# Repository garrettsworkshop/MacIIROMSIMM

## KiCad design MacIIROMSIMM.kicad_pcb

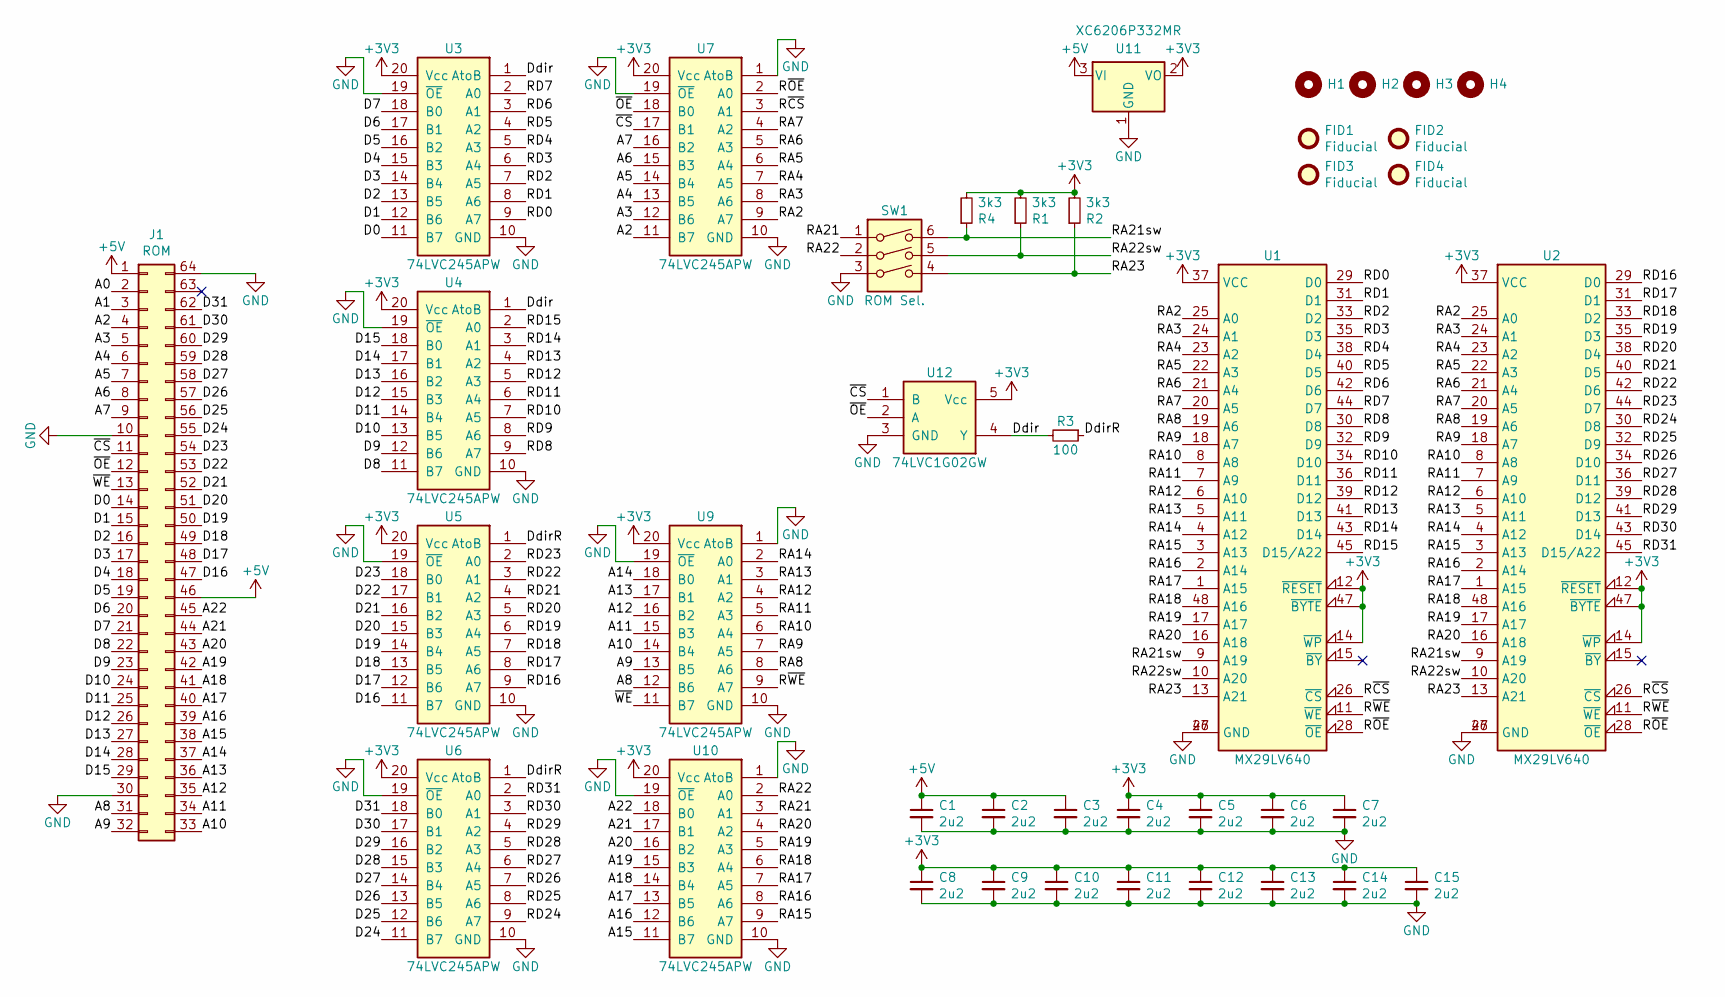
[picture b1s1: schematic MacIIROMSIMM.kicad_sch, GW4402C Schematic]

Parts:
C1, C2, C3, C4, C5, C6, C7, C8, C9, C10, C11, C12, C13, C14, C15: 2u2; C_0603; LCSC Part C23630
FID1, FID2, FID3, FID4: Fiducial
H1, H2, H3, H4: PasteHole_1.152mm_NPTH
J1: ROM; MacIIROMSIMM_Edge
R1, R2, R4: 3k3; R_0603; LCSC Part C22978
R3: 100; R_0603; LCSC Part C22775
SW1: ROM Sel.; SW_DIP_SPSTx03_Slide_DSHP03TS_P1.27mm; LCSC Part C319051
U1, U2: MX29LV640; TSOP-I-48_18.4x12mm_P0.5mm; LCSC Part C30076
U3, U4, U5, U6, U7, U9, U10: 74LVC245APW; TSSOP-20_4.4x6.5mm_P0.65mm; LCSC Part C6082
U11: XC6206P332MR; SOT-23; LCSC Part C5446
U12: 74LVC1G02GW; SOT-353; LCSC Part C353856

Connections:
+3V3: C4.1, C5.1, C6.1, C7.1, C8.1, C9.1, C10.1, C11.1, C12.1, C13.1, C14.1, C15.1, R1.2, R2.2, R4.2, U1.12 (~RESET), U1.14 (~WP), U1.37 (VCC), U1.47 (~BYTE), U2.12 (~RESET), U2.14 (~WP), U2.37 (VCC), U2.47 (~BYTE), U3.20 (Vcc), U4.20 (Vcc), U5.20 (Vcc), U6.20 (Vcc), U7.20 (Vcc), U9.20 (Vcc), U10.20 (Vcc), U11.2 (VO), U12.5 (Vcc)
+5V: C1.1, C2.1, C3.1, J1.1, J1.46, U11.3 (VI)
/A0: J1.2
/A1: J1.3
/A2: J1.4, U7.11 (B7)
/A3: J1.5, U7.12 (B6)
/A4: J1.6, U7.13 (B5)
/A5: J1.7, U7.14 (B4)
/A6: J1.8, U7.15 (B3)
/A7: J1.9, U7.16 (B2)
/A8: J1.31, U9.12 (B6)
/A9: J1.32, U9.13 (B5)
/A10: J1.33, U9.14 (B4)
/A11: J1.34, U9.15 (B3)
/A12: J1.35, U9.16 (B2)
/A13: J1.36, U9.17 (B1)
/A14: J1.37, U9.18 (B0)
/A15: J1.38, U10.11 (B7)
/A16: J1.39, U10.12 (B6)
/A17: J1.40, U10.13 (B5)
/A18: J1.41, U10.14 (B4)
/A19: J1.42, U10.15 (B3)
/A20: J1.43, U10.16 (B2)
/A21: J1.44, U10.17 (B1)
/A22: J1.45, U10.18 (B0)
/D0: J1.14, U3.11 (B7)
/D1: J1.15, U3.12 (B6)
/D2: J1.16, U3.13 (B5)
/D3: J1.17, U3.14 (B4)
/D4: J1.18, U3.15 (B3)
/D5: J1.19, U3.16 (B2)
/D6: J1.20, U3.17 (B1)
/D7: J1.21, U3.18 (B0)
/D8: J1.22, U4.11 (B7)
/D9: J1.23, U4.12 (B6)
/D10: J1.24, U4.13 (B5)
/D11: J1.25, U4.14 (B4)
/D12: J1.26, U4.15 (B3)
/D13: J1.27, U4.16 (B2)
/D14: J1.28, U4.17 (B1)
/D15: J1.29, U4.18 (B0)
/D16: J1.47, U5.11 (B7)
/D17: J1.48, U5.12 (B6)
/D18: J1.49, U5.13 (B5)
/D19: J1.50, U5.14 (B4)
/D20: J1.51, U5.15 (B3)
/D21: J1.52, U5.16 (B2)
/D22: J1.53, U5.17 (B1)
/D23: J1.54, U5.18 (B0)
/D24: J1.55, U6.11 (B7)
/D25: J1.56, U6.12 (B6)
/D26: J1.57, U6.13 (B5)
/D27: J1.58, U6.14 (B4)
/D28: J1.59, U6.15 (B3)
/D29: J1.60, U6.16 (B2)
/D30: J1.61, U6.17 (B1)
/D31: J1.62, U6.18 (B0)
/Ddir: R3.2, U3.1 (AtoB), U4.1 (AtoB), U12.4 (Y)
/DdirR: R3.1, U5.1 (AtoB), U6.1 (AtoB)
/RA2: U1.25 (A0), U2.25 (A0), U7.9 (A7)
/RA3: U1.24 (A1), U2.24 (A1), U7.8 (A6)
/RA4: U1.23 (A2), U2.23 (A2), U7.7 (A5)
/RA5: U1.22 (A3), U2.22 (A3), U7.6 (A4)
/RA6: U1.21 (A4), U2.21 (A4), U7.5 (A3)
/RA7: U1.20 (A5), U2.20 (A5), U7.4 (A2)
/RA8: U1.19 (A6), U2.19 (A6), U9.8 (A6)
/RA9: U1.18 (A7), U2.18 (A7), U9.7 (A5)
/RA10: U1.8 (A8), U2.8 (A8), U9.6 (A4)
/RA11: U1.7 (A9), U2.7 (A9), U9.5 (A3)
/RA12: U1.6 (A10), U2.6 (A10), U9.4 (A2)
/RA13: U1.5 (A11), U2.5 (A11), U9.3 (A1)
/RA14: U1.4 (A12), U2.4 (A12), U9.2 (A0)
/RA15: U1.3 (A13), U2.3 (A13), U10.9 (A7)
/RA16: U1.2 (A14), U2.2 (A14), U10.8 (A6)
/RA17: U1.1 (A15), U2.1 (A15), U10.7 (A5)
/RA18: U1.48 (A16), U2.48 (A16), U10.6 (A4)
/RA19: U1.17 (A17), U2.17 (A17), U10.5 (A3)
/RA20: U1.16 (A18), U2.16 (A18), U10.4 (A2)
/RA21: SW1.1, U10.3 (A1)
/RA21sw: R4.1, SW1.6, U1.9 (A19), U2.9 (A19)
/RA22: SW1.2, U10.2 (A0)
/RA22sw: R1.1, SW1.5, U1.10 (A20), U2.10 (A20)
/RA23: R2.1, SW1.4, U1.13 (A21), U2.13 (A21)
/RD0: U1.29 (D0), U3.9 (A7)
/RD1: U1.31 (D1), U3.8 (A6)
/RD2: U1.33 (D2), U3.7 (A5)
/RD3: U1.35 (D3), U3.6 (A4)
/RD4: U1.38 (D4), U3.5 (A3)
/RD5: U1.40 (D5), U3.4 (A2)
/RD6: U1.42 (D6), U3.3 (A1)
/RD7: U1.44 (D7), U3.2 (A0)
/RD8: U1.30 (D8), U4.9 (A7)
/RD9: U1.32 (D9), U4.8 (A6)
/RD10: U1.34 (D10), U4.7 (A5)
/RD11: U1.36 (D11), U4.6 (A4)
/RD12: U1.39 (D12), U4.5 (A3)
/RD13: U1.41 (D13), U4.4 (A2)
/RD14: U1.43 (D14), U4.3 (A1)
/RD15: U1.45 (D15/A22), U4.2 (A0)
/RD16: U2.29 (D0), U5.9 (A7)
/RD17: U2.31 (D1), U5.8 (A6)
/RD18: U2.33 (D2), U5.7 (A5)
/RD19: U2.35 (D3), U5.6 (A4)
/RD20: U2.38 (D4), U5.5 (A3)
/RD21: U2.40 (D5), U5.4 (A2)
/RD22: U2.42 (D6), U5.3 (A1)
/RD23: U2.44 (D7), U5.2 (A0)
/RD24: U2.30 (D8), U6.9 (A7)
/RD25: U2.32 (D9), U6.8 (A6)
/RD26: U2.34 (D10), U6.7 (A5)
/RD27: U2.36 (D11), U6.6 (A4)
/RD28: U2.39 (D12), U6.5 (A3)
/RD29: U2.41 (D13), U6.4 (A2)
/RD30: U2.43 (D14), U6.3 (A1)
/RD31: U2.45 (D15/A22), U6.2 (A0)
/R~CS: U1.26 (~CS), U2.26 (~CS), U7.3 (A1)
/R~OE: U1.28 (~OE), U2.28 (~OE), U7.2 (A0)
/R~WE: U1.11 (~WE), U2.11 (~WE), U9.9 (A7)
/~CS: J1.11, U7.17 (B1), U12.1 (B)
/~OE: J1.12, U7.18 (B0), U12.2 (A)
/~WE: J1.13, U9.11 (B7)
GND: C1.2, C2.2, C3.2, C4.2, C5.2, C6.2, C7.2, C8.2, C9.2, C10.2, C11.2, C12.2, C13.2, C14.2, C15.2, J1.10, J1.30, J1.64, SW1.3, U1.27 (GND), U1.46 (GND), U2.27 (GND), U2.46 (GND), U3.10 (GND), U3.19 (~OE), U4.10 (GND), U4.19 (~OE), U5.10 (GND), U5.19 (~OE), U6.10 (GND), U6.19 (~OE), U7.1 (AtoB), U7.10 (GND), U7.19 (~OE), U9.1 (AtoB), U9.10 (GND), U9.19 (~OE), U10.1 (AtoB), U10.10 (GND), U10.19 (~OE), U11.1 (GND), U12.3 (GND)

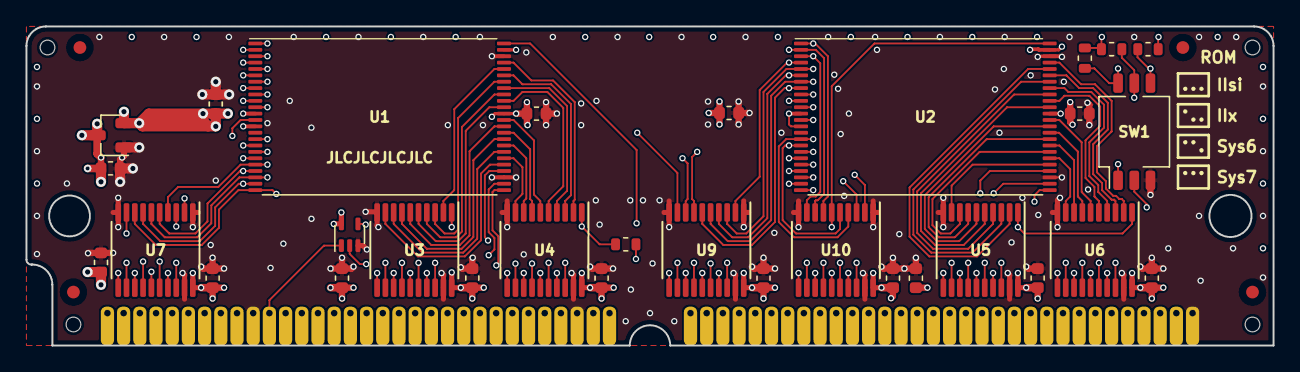
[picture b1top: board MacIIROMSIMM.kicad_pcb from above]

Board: 4 copper layers, 97.8 x 25.0 mm, 40 parts (0 on the bottom side), 120 nets.

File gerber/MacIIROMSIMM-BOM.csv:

"Reference","Quantity","Value","Footprint","LCSC Part","DNP"
"C1, C2, C3, C4, C5, C6, C7, C8, C9, C10, C11, C12, C13, C14, C15","15","2u2","stdpads:C_0603","C23630",""
"FID1, FID2, FID3, FID4","4","Fiducial","stdpads:Fiducial","",""
"H1, H2, H3, H4","4","","stdpads:PasteHole_1.152mm_NPTH","",""
"J1","1","ROM","stdpads:MacIIROMSIMM_Edge","",""
"R1, R2, R4","3","3k3","stdpads:R_0603","C22978",""
"R3","1","100","stdpads:R_0603","C22775",""
"SW1","1","ROM Sel.","stdpads:SW_DIP_SPSTx03_Slide_DSHP03TS_P1.27mm","C319051",""
"U1, U2","2","MX29LV640","stdpads:TSOP-I-48_18.4x12mm_P0.5mm","C30076",""
"U3, U4, U5, U6, U7, U9, U10","7","74LVC245APW","stdpads:TSSOP-20_4.4x6.5mm_P0.65mm","C6082",""
"U11","1","XC6206P332MR","stdpads:SOT-23","C5446",""
"U12","1","74LVC1G02GW","stdpads:SOT-353","C353856",""

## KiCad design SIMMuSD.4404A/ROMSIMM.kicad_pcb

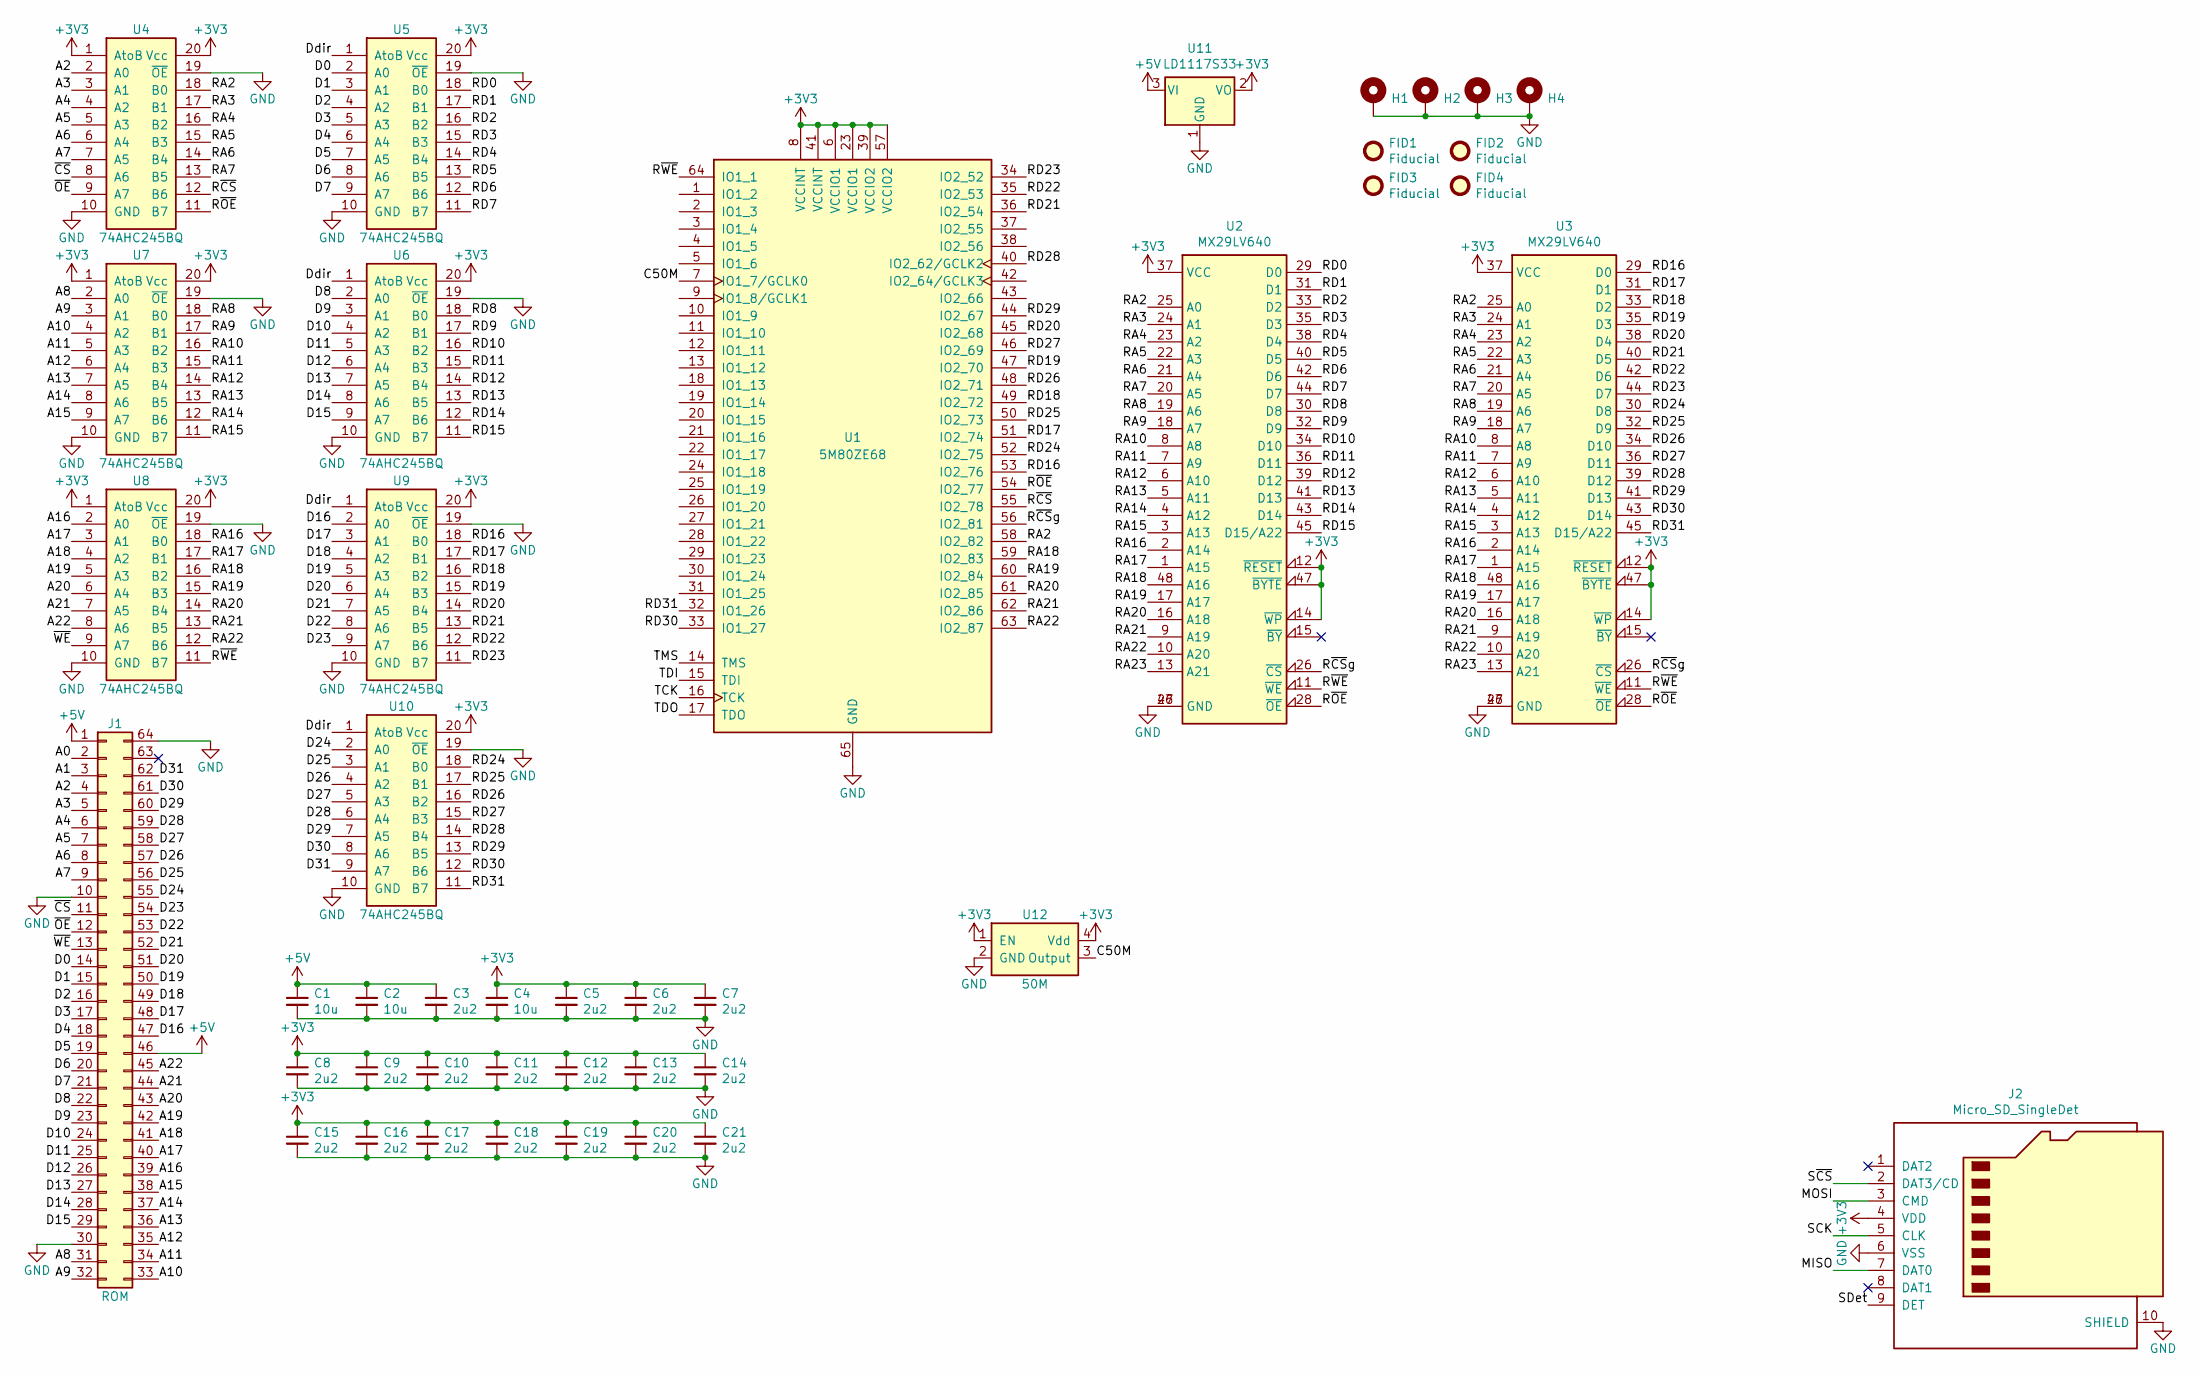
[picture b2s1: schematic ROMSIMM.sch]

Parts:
C1, C2, C4: 10u; C_0805
C3, C5, C6, C7, C8, C9, C10, C11, C12, C13, C14, C15, C16, C17, C18, C19, C20, C21: 2u2; C_0603
FID1, FID2, FID3, FID4: Fiducial
H1, H2, H3, H4: PasteHole_1.1mm_PTH
J1: ROM; MacIIROMSIMM_Edge
J2: Micro_SD_SingleDet
U1: 5M80ZE68; EQFP-64_10x10mm_P0.5mm
U2, U3: MX29LV640; TSOP-I-48_18.4x12mm_P0.5mm
U4, U5, U6, U7, U8, U9, U10: 74AHC245BQ; Nexperia_DHVFQFN-20_SOT764-1
U11: LD1117S33; SOT-223
U12: 50M

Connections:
+3V3: C4.1, C5.1, C6.1, C7.1, C8.1, C9.1, C10.1, C11.1, C12.1, C13.1, C14.1, C15.1, C16.1, C17.1, C18.1, C19.1, C20.1, C21.1, J2.4 (VDD), U1.6 (VCCIO1), U1.8 (VCCINT), U1.23 (VCCIO1), U1.39 (VCCIO2), U1.41 (VCCINT), U1.57 (VCCIO2), U2.12 (~RESET~), U2.14 (~WP~), U2.37 (VCC), U2.47 (~BYTE~), U3.12 (~RESET~), U3.14 (~WP~), U3.37 (VCC), U3.47 (~BYTE~), U4.1 (AtoB), U4.20 (Vcc), U5.20 (Vcc), U6.20 (Vcc), U7.1 (AtoB), U7.20 (Vcc), U8.1 (AtoB), U8.20 (Vcc), U9.20 (Vcc), U10.20 (Vcc), U11.2 (VO), U12.1 (EN), U12.4 (Vdd); also elsewhere on the board
+5V: C1.1, C2.1, C3.1, J1.1, J1.46, U11.3 (VI)
/A0: J1.2
/A1: J1.3
/A2: J1.4, U4.2 (A0)
/A3: J1.5, U4.3 (A1)
/A4: J1.6, U4.4 (A2)
/A5: J1.7, U4.5 (A3)
/A6: J1.8, U4.6 (A4)
/A7: J1.9, U4.7 (A5)
/A8: J1.31, U7.2 (A0)
/A9: J1.32, U7.3 (A1)
/A10: J1.33, U7.4 (A2)
/A11: J1.34, U7.5 (A3)
/A12: J1.35, U7.6 (A4)
/A13: J1.36, U7.7 (A5)
/A14: J1.37, U7.8 (A6)
/A15: J1.38, U7.9 (A7)
/A16: J1.39, U8.2 (A0)
/A17: J1.40, U8.3 (A1)
/A18: J1.41, U8.4 (A2)
/A19: J1.42, U8.5 (A3)
/A20: J1.43, U8.6 (A4)
/A21: J1.44, U8.7 (A5)
/A22: J1.45, U8.8 (A6)
/C50M: U1.7 (IO1_7/GCLK0), U12.3 (Output)
/D0: J1.14, U5.2 (A0)
/D1: J1.15, U5.3 (A1)
/D2: J1.16, U5.4 (A2)
/D3: J1.17, U5.5 (A3)
/D4: J1.18, U5.6 (A4)
/D5: J1.19, U5.7 (A5)
/D6: J1.20, U5.8 (A6)
/D7: J1.21, U5.9 (A7)
/D8: J1.22, U6.2 (A0)
/D9: J1.23, U6.3 (A1)
/D10: J1.24, U6.4 (A2)
/D11: J1.25, U6.5 (A3)
/D12: J1.26, U6.6 (A4)
/D13: J1.27, U6.7 (A5)
/D14: J1.28, U6.8 (A6)
/D15: J1.29, U6.9 (A7)
/D16: J1.47, U9.2 (A0)
/D17: J1.48, U9.3 (A1)
/D18: J1.49, U9.4 (A2)
/D19: J1.50, U9.5 (A3)
/D20: J1.51, U9.6 (A4)
/D21: J1.52, U9.7 (A5)
/D22: J1.53, U9.8 (A6)
/D23: J1.54, U9.9 (A7)
/D24: J1.55, U10.2 (A0)
/D25: J1.56, U10.3 (A1)
/D26: J1.57, U10.4 (A2)
/D27: J1.58, U10.5 (A3)
/D28: J1.59, U10.6 (A4)
/D29: J1.60, U10.7 (A5)
/D30: J1.61, U10.8 (A6)
/D31: J1.62, U10.9 (A7)
/Ddir: U5.1 (AtoB), U6.1 (AtoB), U9.1 (AtoB), U10.1 (AtoB)
/MISO: J2.7 (DAT0)
/MOSI: J2.3 (CMD)
/RA2: U1.58 (IO2_82), U2.25 (A0), U3.25 (A0), U4.18 (B0)
/RA3: U2.24 (A1), U3.24 (A1), U4.17 (B1)
/RA4: U2.23 (A2), U3.23 (A2), U4.16 (B2)
/RA5: U2.22 (A3), U3.22 (A3), U4.15 (B3)
/RA6: U2.21 (A4), U3.21 (A4), U4.14 (B4)
/RA7: U2.20 (A5), U3.20 (A5), U4.13 (B5)
/RA8: U2.19 (A6), U3.19 (A6), U7.18 (B0)
/RA9: U2.18 (A7), U3.18 (A7), U7.17 (B1)
/RA10: U2.8 (A8), U3.8 (A8), U7.16 (B2)
/RA11: U2.7 (A9), U3.7 (A9), U7.15 (B3)
/RA12: U2.6 (A10), U3.6 (A10), U7.14 (B4)
/RA13: U2.5 (A11), U3.5 (A11), U7.13 (B5)
/RA14: U2.4 (A12), U3.4 (A12), U7.12 (B6)
/RA15: U2.3 (A13), U3.3 (A13), U7.11 (B7)
/RA16: U2.2 (A14), U3.2 (A14), U8.18 (B0)
/RA17: U2.1 (A15), U3.1 (A15), U8.17 (B1)
/RA18: U1.59 (IO2_83), U2.48 (A16), U3.48 (A16), U8.16 (B2)
/RA19: U1.60 (IO2_84), U2.17 (A17), U3.17 (A17), U8.15 (B3)
/RA20: U1.61 (IO2_85), U2.16 (A18), U3.16 (A18), U8.14 (B4)
/RA21: U1.62 (IO2_86), U2.9 (A19), U3.9 (A19), U8.13 (B5)
/RA22: U1.63 (IO2_87), U2.10 (A20), U3.10 (A20), U8.12 (B6)
/RA23: U2.13 (A21), U3.13 (A21)
/RD0: U2.29 (D0), U5.18 (B0)
/RD1: U2.31 (D1), U5.17 (B1)
/RD2: U2.33 (D2), U5.16 (B2)
/RD3: U2.35 (D3), U5.15 (B3)
/RD4: U2.38 (D4), U5.14 (B4)
/RD5: U2.40 (D5), U5.13 (B5)
/RD6: U2.42 (D6), U5.12 (B6)
/RD7: U2.44 (D7), U5.11 (B7)
/RD8: U2.30 (D8), U6.18 (B0)
/RD9: U2.32 (D9), U6.17 (B1)
/RD10: U2.34 (D10), U6.16 (B2)
/RD11: U2.36 (D11), U6.15 (B3)
/RD12: U2.39 (D12), U6.14 (B4)
/RD13: U2.41 (D13), U6.13 (B5)
/RD14: U2.43 (D14), U6.12 (B6)
/RD15: U2.45 (D15/A22), U6.11 (B7)
/RD16: U1.53 (IO2_76), U3.29 (D0), U9.18 (B0)
/RD17: U1.51 (IO2_74), U3.31 (D1), U9.17 (B1)
/RD18: U1.49 (IO2_72), U3.33 (D2), U9.16 (B2)
/RD19: U1.47 (IO2_70), U3.35 (D3), U9.15 (B3)
/RD20: U1.45 (IO2_68), U3.38 (D4), U9.14 (B4)
/RD21: U1.36 (IO2_54), U3.40 (D5), U9.13 (B5)
/RD22: U1.35 (IO2_53), U3.42 (D6), U9.12 (B6)
/RD23: U1.34 (IO2_52), U3.44 (D7), U9.11 (B7)
/RD24: U1.52 (IO2_75), U3.30 (D8), U10.18 (B0)
/RD25: U1.50 (IO2_73), U3.32 (D9), U10.17 (B1)
/RD26: U1.48 (IO2_71), U3.34 (D10), U10.16 (B2)
/RD27: U1.46 (IO2_69), U3.36 (D11), U10.15 (B3)
/RD28: U1.40 (IO2_62/GCLK2), U3.39 (D12), U10.14 (B4)
/RD29: U1.44 (IO2_67), U3.41 (D13), U10.13 (B5)
/RD30: U1.33 (IO1_27), U3.43 (D14), U10.12 (B6)
/RD31: U1.32 (IO1_26), U3.45 (D15/A22), U10.11 (B7)
/R~CS~: U1.55 (IO2_78), U4.12 (B6)
/R~CS~g: U1.56 (IO2_81), U2.26 (~CS~), U3.26 (~CS~)
/R~OE~: U1.54 (IO2_77), U2.28 (~OE~), U3.28 (~OE~), U4.11 (B7)
/R~WE~: U1.64 (IO1_1), U2.11 (~WE~), U3.11 (~WE~), U8.11 (B7)
/SCK: J2.5 (CLK)
/SDet: J2.9 (DET)
/S~CS~: J2.2 (DAT3/CD)
/TCK: U1.16 (TCK)
/TDI: U1.15 (TDI)
/TDO: U1.17 (TDO)
/TMS: U1.14 (TMS)
/~CS~: J1.11, U4.8 (A6)
/~OE~: J1.12, U4.9 (A7)
/~WE~: J1.13, U8.9 (A7)
GND: C1.2, C2.2, C3.2, C4.2, C5.2, C6.2, C7.2, C8.2, C9.2, C10.2, C11.2, C12.2, C13.2, C14.2, C15.2, C16.2, C17.2, C18.2, C19.2, C20.2, C21.2, H1.1, H2.1, H3.1, H4.1, J1.10, J1.30, J1.64, J2.6 (VSS), J2.10 (SHIELD), U1.65 (GND), U2.27 (GND), U2.46 (GND), U3.27 (GND), U3.46 (GND), U4.10 (GND), U4.19 (~OE~), U4.21 (pad), U5.10 (GND), U5.19 (~OE~), U5.21 (pad), U6.10 (GND), U6.19 (~OE~), U6.21 (pad), U7.10 (GND), U7.19 (~OE~), U7.21 (pad), U8.10 (GND), U8.19 (~OE~), U8.21 (pad), U9.10 (GND), U9.19 (~OE~), U9.21 (pad), U10.10 (GND), U10.19 (~OE~), U10.21 (pad), U11.1 (GND), U12.2 (GND)

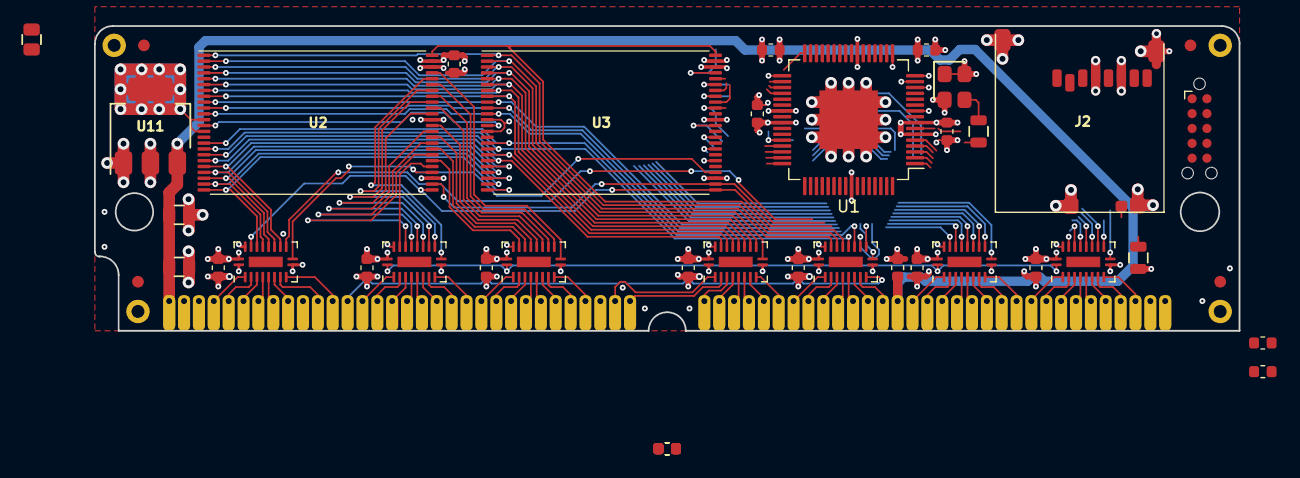
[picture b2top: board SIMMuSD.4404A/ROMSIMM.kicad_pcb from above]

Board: 4 copper layers, 97.8 x 26.0 mm, 46 parts (0 on the bottom side), 119 nets.

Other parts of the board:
J3: Tag-Connect_TC2050-IDC-NL_2x05_P1.27mm_Vertical
R1, R1#2: 3k3; R_0805

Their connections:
+3V3: R1#2.1; also elsewhere on the board

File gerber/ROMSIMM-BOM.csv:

"Ref","Qnty","Value","Cmp name","Footprint","Description","Vendor","LCSC Part"
"C1, C2, C3, C4, C5, C6, C7, C8, C9, C10, C11, C12, C13, C14, C15, ","15","2u2","C_Small","stdpads:C_0603","Unpolarized capacitor, small symbol","","C23630"
"FID1, FID2, FID3, FID4, ","4","Fiducial","Fiducial","stdpads:Fiducial","Fiducial Marker","",""
"H1, H2, H3, H4, ","4","","MountingHole_Pad","stdpads:PasteHole_1.152mm_NPTH","Mounting Hole with connection","",""
"J1, ","1","ROM","Conn_02x32_Counter_Clockwise","stdpads:MacIIROMSIMM_Edge","Generic connector, double row, 02x32, counter clockwise pin numbering scheme (similar to DIP packge numbering), script generated (kicad-library-utils/schlib/autogen/connector/)","",""
"R1, R2, R4, ","3","3k3","R_Small","stdpads:R_0603","Resistor, small symbol","","C22978"
"R3, ","1","100","R_Small","stdpads:R_0603","Resistor, small symbol","","C22775"
"SW1, ","1","ROM Sel.","SW_DIP_x03","stdpads:SW_DIP_SPSTx03_Slide_DSHP03TS_P1.27mm","3x DIP Switch, Single Pole Single Throw (SPST) switch, small symbol","","C319052"
"U1, U2, ","2","MX29LV640","Flash-4Mx16-TSOP1-48","stdpads:TSOP-I-48_18.4x12mm_P0.5mm","","","C117907"
"U3, U4, U5, U6, U7, U9, U10, ","7","74AHC245","74245","stdpads:TSSOP-20_4.4x6.5mm_P0.65mm","","","C132987"
"U11, ","1","XC6206P332MR","XC6206PxxxMR","stdpads:SOT-23","Positive 60-250mA Low Dropout Regulator, Fixed Output, SOT-23","","C5446"
"U12, ","1","74LVC1G02GW","741G02GW","stdpads:SOT-353","","","C353856"

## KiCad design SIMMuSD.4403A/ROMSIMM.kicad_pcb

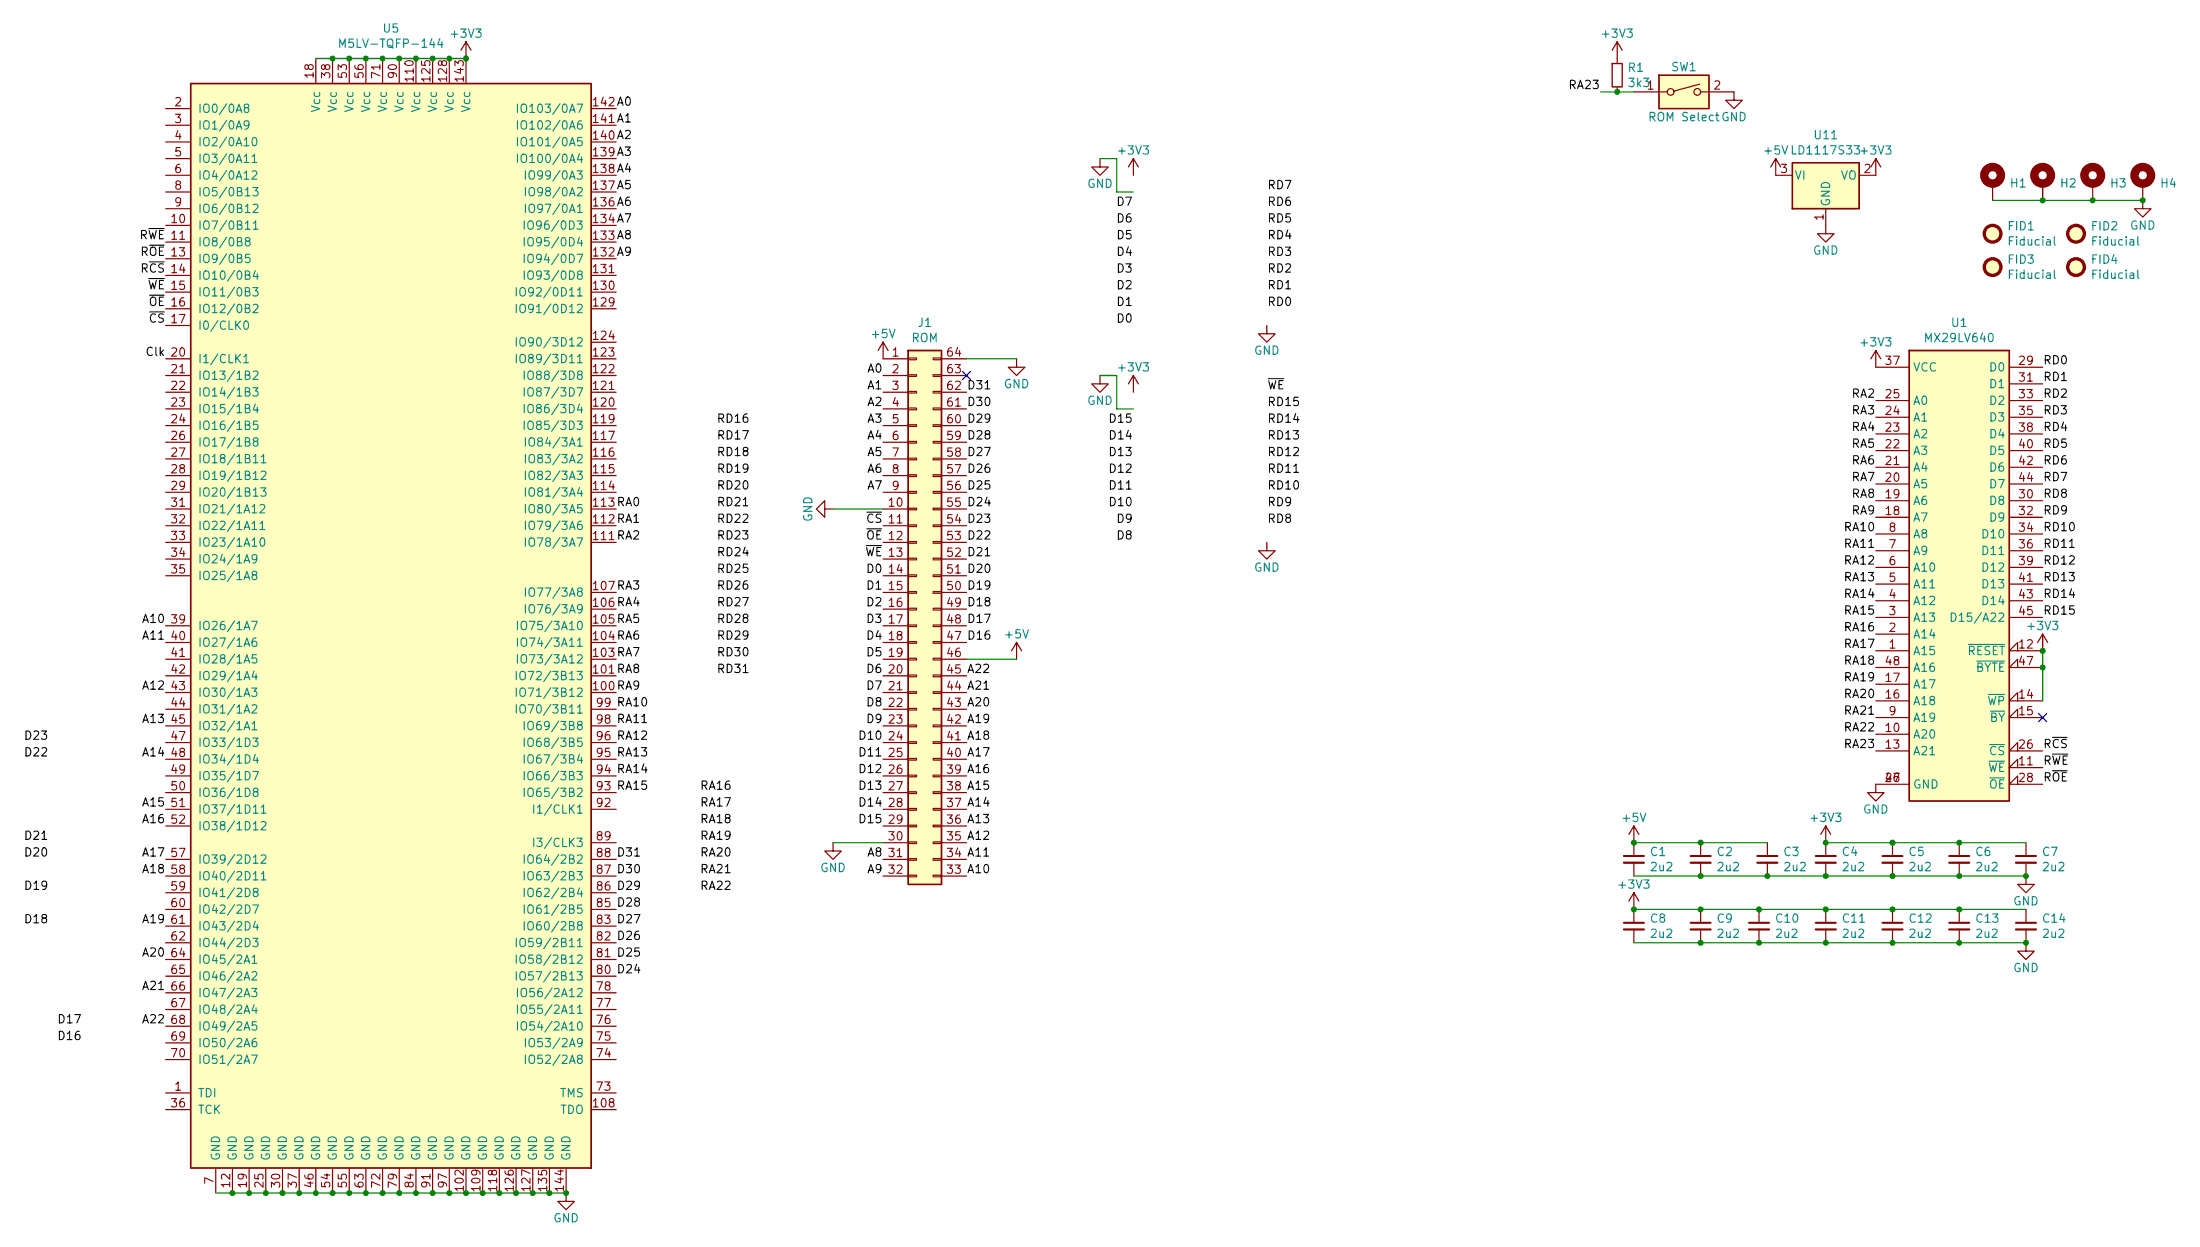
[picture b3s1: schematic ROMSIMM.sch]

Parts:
C1, C2, C3, C4, C5, C6, C7, C8, C9, C10, C11, C12, C13, C14: 2u2; C_0603
FID1, FID2, FID3, FID4: Fiducial
H1, H2, H3, H4: PasteHole_1.1mm_PTH
J1: ROM; MacIIROMSIMM_Edge
R1: 3k3; R_0805
SW1: ROM Select
U1: MX29LV640; TSOP-I-48_18.4x12mm_P0.5mm
U5: M5LV-TQFP-144; TQFP-144_20x20mm_P0.5mm
U11: LD1117S33; SOT-223

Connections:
+3V3: C4.1, C5.1, C6.1, C7.1, C8.1, C9.1, C10.1, C11.1, C12.1, C13.1, C14.1, R1.1, U1.12 (~RESET~), U1.14 (~WP~), U1.37 (VCC), U1.47 (~BYTE~), U5.18 (Vcc), U5.38 (Vcc), U5.53 (Vcc), U5.56 (Vcc), U5.71 (Vcc), U5.90 (Vcc), U5.110 (Vcc), U5.125 (Vcc), U5.128 (Vcc), U5.143 (Vcc), U11.2 (VO)
+5V: C1.1, C2.1, C3.1, J1.1, J1.46, U11.3 (VI)
/A0: J1.2, U5.142 (IO103/0A7)
/A1: J1.3, U5.141 (IO102/0A6)
/A2: J1.4, U5.140 (IO101/0A5)
/A3: J1.5, U5.139 (IO100/0A4)
/A4: J1.6, U5.138 (IO99/0A3)
/A5: J1.7, U5.137 (IO98/0A2)
/A6: J1.8, U5.136 (IO97/0A1)
/A7: J1.9, U5.44 (IO31/1A2), U5.134 (IO96/0D3)
/A8: J1.31, U5.42 (IO29/1A4), U5.133 (IO95/0D4)
/A9: J1.32, U5.41 (IO28/1A5), U5.132 (IO94/0D7)
/A10: J1.33, U5.39 (IO26/1A7)
/A11: J1.34, U5.40 (IO27/1A6)
/A12: J1.35, U5.43 (IO30/1A3)
/A13: J1.36, U5.45 (IO32/1A1)
/A14: J1.37, U5.48 (IO34/1D4)
/A15: J1.38, U5.51 (IO37/1D11)
/A16: J1.39, U5.52 (IO38/1D12)
/A17: J1.40, U5.57 (IO39/2D12)
/A18: J1.41, U5.58 (IO40/2D11)
/A19: J1.42, U5.61 (IO43/2D4)
/A20: J1.43, U5.64 (IO45/2A1)
/A21: J1.44, U5.66 (IO47/2A3)
/A22: J1.45, U5.68 (IO49/2A5)
/Clk: U5.20 (I1/CLK1)
/D0: J1.14
/D1: J1.15
/D2: J1.16
/D3: J1.17
/D4: J1.18
/D5: J1.19
/D6: J1.20
/D7: J1.21
/D8: J1.22
/D9: J1.23
/D10: J1.24
/D11: J1.25
/D12: J1.26
/D13: J1.27
/D14: J1.28
/D15: J1.29
/D16: J1.47
/D17: J1.48
/D18: J1.49
/D19: J1.50
/D20: J1.51
/D21: J1.52
/D22: J1.53
/D23: J1.54
/D24: J1.55, U5.80 (IO57/2B13)
/D25: J1.56, U5.81 (IO58/2B12)
/D26: J1.57, U5.82 (IO59/2B11)
/D27: J1.58, U5.83 (IO60/2B8)
/D28: J1.59, U5.85 (IO61/2B5)
/D29: J1.60, U5.86 (IO62/2B4)
/D30: J1.61, U5.87 (IO63/2B3)
/D31: J1.62, U5.88 (IO64/2B2)
/RA0: U5.113 (IO80/3A5)
/RA1: U5.112 (IO79/3A6)
/RA2: U1.25 (A0), U5.111 (IO78/3A7)
/RA3: U1.24 (A1), U5.107 (IO77/3A8)
/RA4: U1.23 (A2), U5.106 (IO76/3A9)
/RA5: U1.22 (A3), U5.105 (IO75/3A10)
/RA6: U1.21 (A4), U5.104 (IO74/3A11)
/RA7: U1.20 (A5), U5.103 (IO73/3A12)
/RA8: U1.19 (A6), U5.101 (IO72/3B13)
/RA9: U1.18 (A7), U5.100 (IO71/3B12)
/RA10: U1.8 (A8), U5.99 (IO70/3B11)
/RA11: U1.7 (A9), U5.98 (IO69/3B8)
/RA12: U1.6 (A10), U5.96 (IO68/3B5)
/RA13: U1.5 (A11), U5.95 (IO67/3B4)
/RA14: U1.4 (A12), U5.94 (IO66/3B3)
/RA15: U1.3 (A13), U5.93 (IO65/3B2)
/RA16: U1.2 (A14)
/RA17: U1.1 (A15)
/RA18: U1.48 (A16)
/RA19: U1.17 (A17)
/RA20: U1.16 (A18)
/RA21: U1.9 (A19)
/RA22: U1.10 (A20)
/RA23: R1.2, SW1.1, U1.13 (A21)
/RD16: U1.29 (D0)
/RD17: U1.31 (D1)
/RD18: U1.33 (D2)
/RD19: U1.35 (D3)
/RD20: U1.38 (D4)
/RD21: U1.40 (D5)
/RD22: U1.42 (D6)
/RD23: U1.44 (D7)
/RD24: U1.30 (D8)
/RD25: U1.32 (D9)
/RD26: U1.34 (D10)
/RD27: U1.36 (D11)
/RD28: U1.39 (D12)
/RD29: U1.41 (D13)
/RD30: U1.43 (D14)
/RD31: U1.45 (D15/A22)
/R~CS~: U1.26 (~CS~), U5.14 (IO10/0B4)
/R~OE~: U1.28 (~OE~), U5.13 (IO9/0B5)
/R~WE~: U1.11 (~WE~), U5.11 (IO8/0B8)
/~CS~: J1.11, U5.17 (I0/CLK0)
/~OE~: J1.12, U5.16 (IO12/0B2)
/~WE~: J1.13, U5.15 (IO11/0B3)
GND: C1.2, C2.2, C3.2, C4.2, C5.2, C6.2, C7.2, C8.2, C9.2, C10.2, C11.2, C12.2, C13.2, C14.2, H1.1, H2.1, H3.1, H4.1, J1.10, J1.30, J1.64, SW1.2, U1.27 (GND), U1.46 (GND), U5.7 (GND), U5.12 (GND), U5.19 (GND), U5.25 (GND), U5.30 (GND), U5.37 (GND), U5.46 (GND), U5.54 (GND), U5.55 (GND), U5.63 (GND), U5.72 (GND), U5.79 (GND), U5.84 (GND), U5.91 (GND), U5.97 (GND), U5.102 (GND), U5.109 (GND), U5.118 (GND), U5.126 (GND), U5.127 (GND), U5.135 (GND), U5.144 (GND), U11.1 (GND)

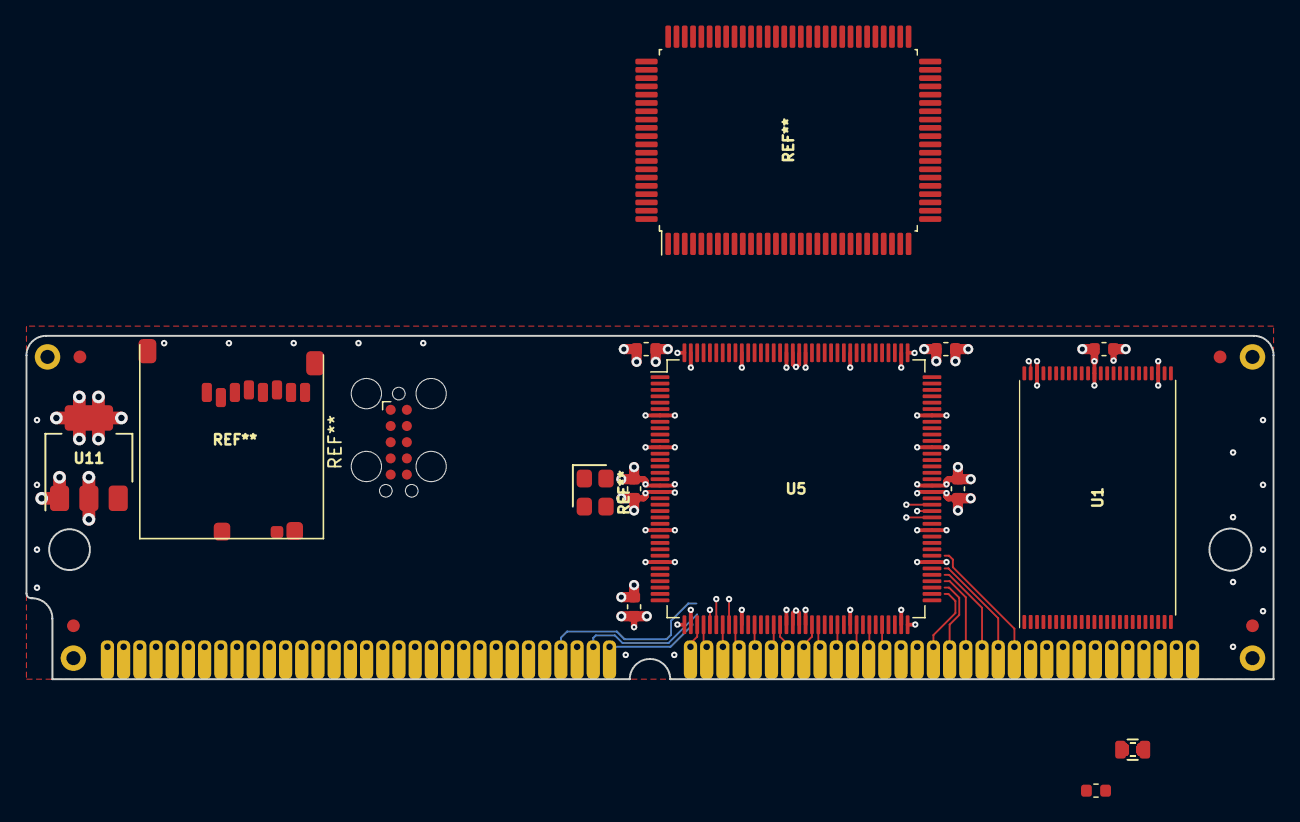
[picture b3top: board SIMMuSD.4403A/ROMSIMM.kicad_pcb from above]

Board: 4 copper layers, 97.8 x 26.9 mm, 27 parts (0 on the bottom side), 55 nets.

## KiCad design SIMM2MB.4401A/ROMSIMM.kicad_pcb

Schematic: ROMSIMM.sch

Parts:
C1, C2, C3, C4: 10u; C_0805
C5, C6: 2u2; C_0603
J1: ROM; MacIIROMSIMM_Edge
U1: D31-24; PLCC-32_SMDSocket
U2: D23-16; PLCC-32_SMDSocket
U3: D15-8; PLCC-32_SMDSocket
U4: D7-0; PLCC-32_SMDSocket

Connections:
+5V: C1.1, C2.1, C3.1, C4.1, C5.1, C6.1, J1.1, J1.46, U1.32, U2.32, U3.32, U4.32
/A0: J1.2
/A1: J1.3
/A2: J1.4, U1.12, U2.12, U3.12, U4.12
/A3: J1.5, U1.11, U2.11, U3.11, U4.11
/A4: J1.6, U1.10, U2.10, U3.10, U4.10
/A5: J1.7, U1.9, U2.9, U3.9, U4.9
/A6: J1.8, U1.8, U2.8, U3.8, U4.8
/A7: J1.9, U1.7, U2.7, U3.7, U4.7
/A8: J1.31, U1.6, U2.6, U3.6, U4.6
/A9: J1.32, U1.5, U2.5, U3.5, U4.5
/A10: J1.33, U1.27, U2.27, U3.27, U4.27
/A11: J1.34, U1.26, U2.26, U3.26, U4.26
/A12: J1.35, U1.23, U2.23, U3.23, U4.23
/A13: J1.36, U1.25, U2.25, U3.25, U4.25
/A14: J1.37, U1.4, U2.4, U3.4, U4.4
/A15: J1.38, U1.28, U2.28, U3.28, U4.28
/A16: J1.39, U1.29, U2.29, U3.29, U4.29
/A17: J1.40, U1.3, U2.3, U3.3, U4.3
/A18: J1.41, U1.2, U2.2, U3.2, U4.2
/A19: J1.42, U1.30, U2.30, U3.30, U4.30
/A20: J1.43, U1.1, U2.1, U3.1, U4.1
/A21: J1.44
/A22: J1.45
/D0: J1.14, U1.13
/D1: J1.15, U1.14
/D2: J1.16, U1.15
/D3: J1.17, U1.17
/D4: J1.18, U1.18
/D5: J1.19, U1.19
/D6: J1.20, U1.20
/D7: J1.21, U1.21
/D8: J1.22, U2.13
/D9: J1.23, U2.14
/D10: J1.24, U2.15
/D11: J1.25, U2.17
/D12: J1.26, U2.18
/D13: J1.27, U2.19
/D14: J1.28, U2.20
/D15: J1.29, U2.21
/D16: J1.47, U3.13
/D17: J1.48, U3.14
/D18: J1.49, U3.15
/D19: J1.50, U3.17
/D20: J1.51, U3.18
/D21: J1.52, U3.19
/D22: J1.53, U3.20
/D23: J1.54, U3.21
/D24: J1.55, U4.13
/D25: J1.56, U4.14
/D26: J1.57, U4.15
/D27: J1.58, U4.17
/D28: J1.59, U4.18
/D29: J1.60, U4.19
/D30: J1.61, U4.20
/D31: J1.62, U4.21
/~CS~: J1.11, U1.22, U2.22, U3.22, U4.22
/~OE~: J1.12, U1.24, U2.24, U3.24, U4.24
/~WE~: J1.13, U1.31, U2.31, U3.31, U4.31
GND: C1.2, C2.2, C3.2, C4.2, C5.2, C6.2, J1.10, J1.30, J1.64, U1.16, U2.16, U3.16, U4.16

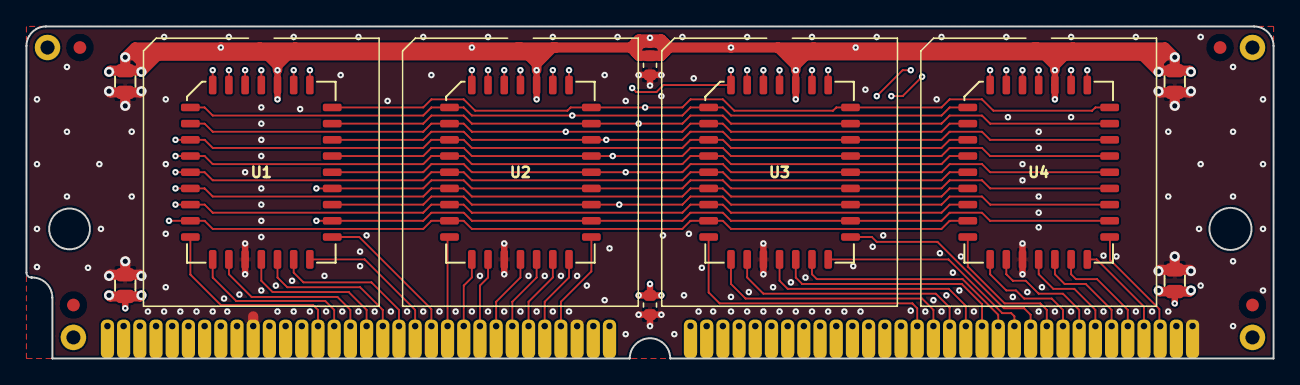
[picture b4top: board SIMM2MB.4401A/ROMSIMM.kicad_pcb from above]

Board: 4 copper layers, 97.8 x 26.0 mm, 19 parts (0 on the bottom side), 56 nets.

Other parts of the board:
FID1, FID2, FID3, FID4: Fiducial
H1, H2, H3, H4: PasteHole_1.1mm_PTH

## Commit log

2020-01-26 started
2020-05-16 asdsda
2020-05-16 Better stitching, with refdes on back
2020-05-16 Rounded corners
2020-05-16 Removed gerbers
2020-05-16 Moved 2MB simm to its own folder
2020-05-16 Added 8MB simm
2020-05-16 Switched GW number of 8MB simm to 4402A
2020-05-16 Added 3d models back to 2MB, also fixed some stitching
2020-05-16 Added renders
2020-05-16 8MB stitching fix
2020-05-16 Unrounded corners on bottom edge of both SIMMS
2020-05-17 8MB idk
2020-05-17 As submitted to JLCPCB
2020-06-22 8MB SIMM as sent to JLCPCB June 2020
2020-06-22 Ad copy for 4401A
2020-06-22 Partial attempt at uSD
2020-06-24 Added probably final 8MB SIMM
2020-06-25 Changed uSD model number to GW4404A
2020-07-02 More uSD
2020-07-02 8MB fixes
2020-07-04 Removed uSD board
2020-07-04 Moved 2MB SIMM
2020-07-06 8MB SIMM as sent to JLCPCB July 2020
2020-07-12 Update Description
2020-07-21 Rename documentation files
2020-07-25 Add compatibility notes to documenation
2020-09-20 Documentation update
2021-04-03 Finished rev. B board
2021-04-03 Draft manual
2021-04-03 Make silkscreen setting text clearer
2021-04-12 Fabbed
2021-04-13 Remove 2 MB SIMM files
2021-04-13 Move 4402B files into mail directory
2021-04-13 Move 4402A files into main directory
2021-04-13 Update footprint and symbol library paths
2021-04-13 Actually fabbed
2021-05-27 Fixed footprint and symbol library relative path
2021-05-31 Renamed manual
2021-06-21 Create LICENSE
2021-06-21 Eliminated one 74AHC245PW
2021-07-01 Update manual
2021-07-01 Remove outdated gerbers
2021-07-01 Add mask cutout for edge connector pins on back
2021-08-06 Manual done?
2022-01-12 Start on triple DIP switch
2022-02-06 Migrate to KiCAD 6
2022-02-13 Done?
2023-01-17 Add new GW logotype
2023-01-17 Revert "Update .gitignore"
    This reverts commit 15efc4c213469be153dbbee9b55e5e993137f9c2.
2023-01-17 Revert "Update .gitignore"
    This reverts commit 4e2181716f4f4b47edfc1a7cbb61e439a322dc94.
2024-02-16 Change project file name to MacIIROMSIMM
2024-02-16 Create Makefile
2024-05-06 idk build?
2024-05-19 Build and changed text to 4402B
2024-05-19 Fix naming in Makefile
2024-05-19 Update makefile to add BOM generation
